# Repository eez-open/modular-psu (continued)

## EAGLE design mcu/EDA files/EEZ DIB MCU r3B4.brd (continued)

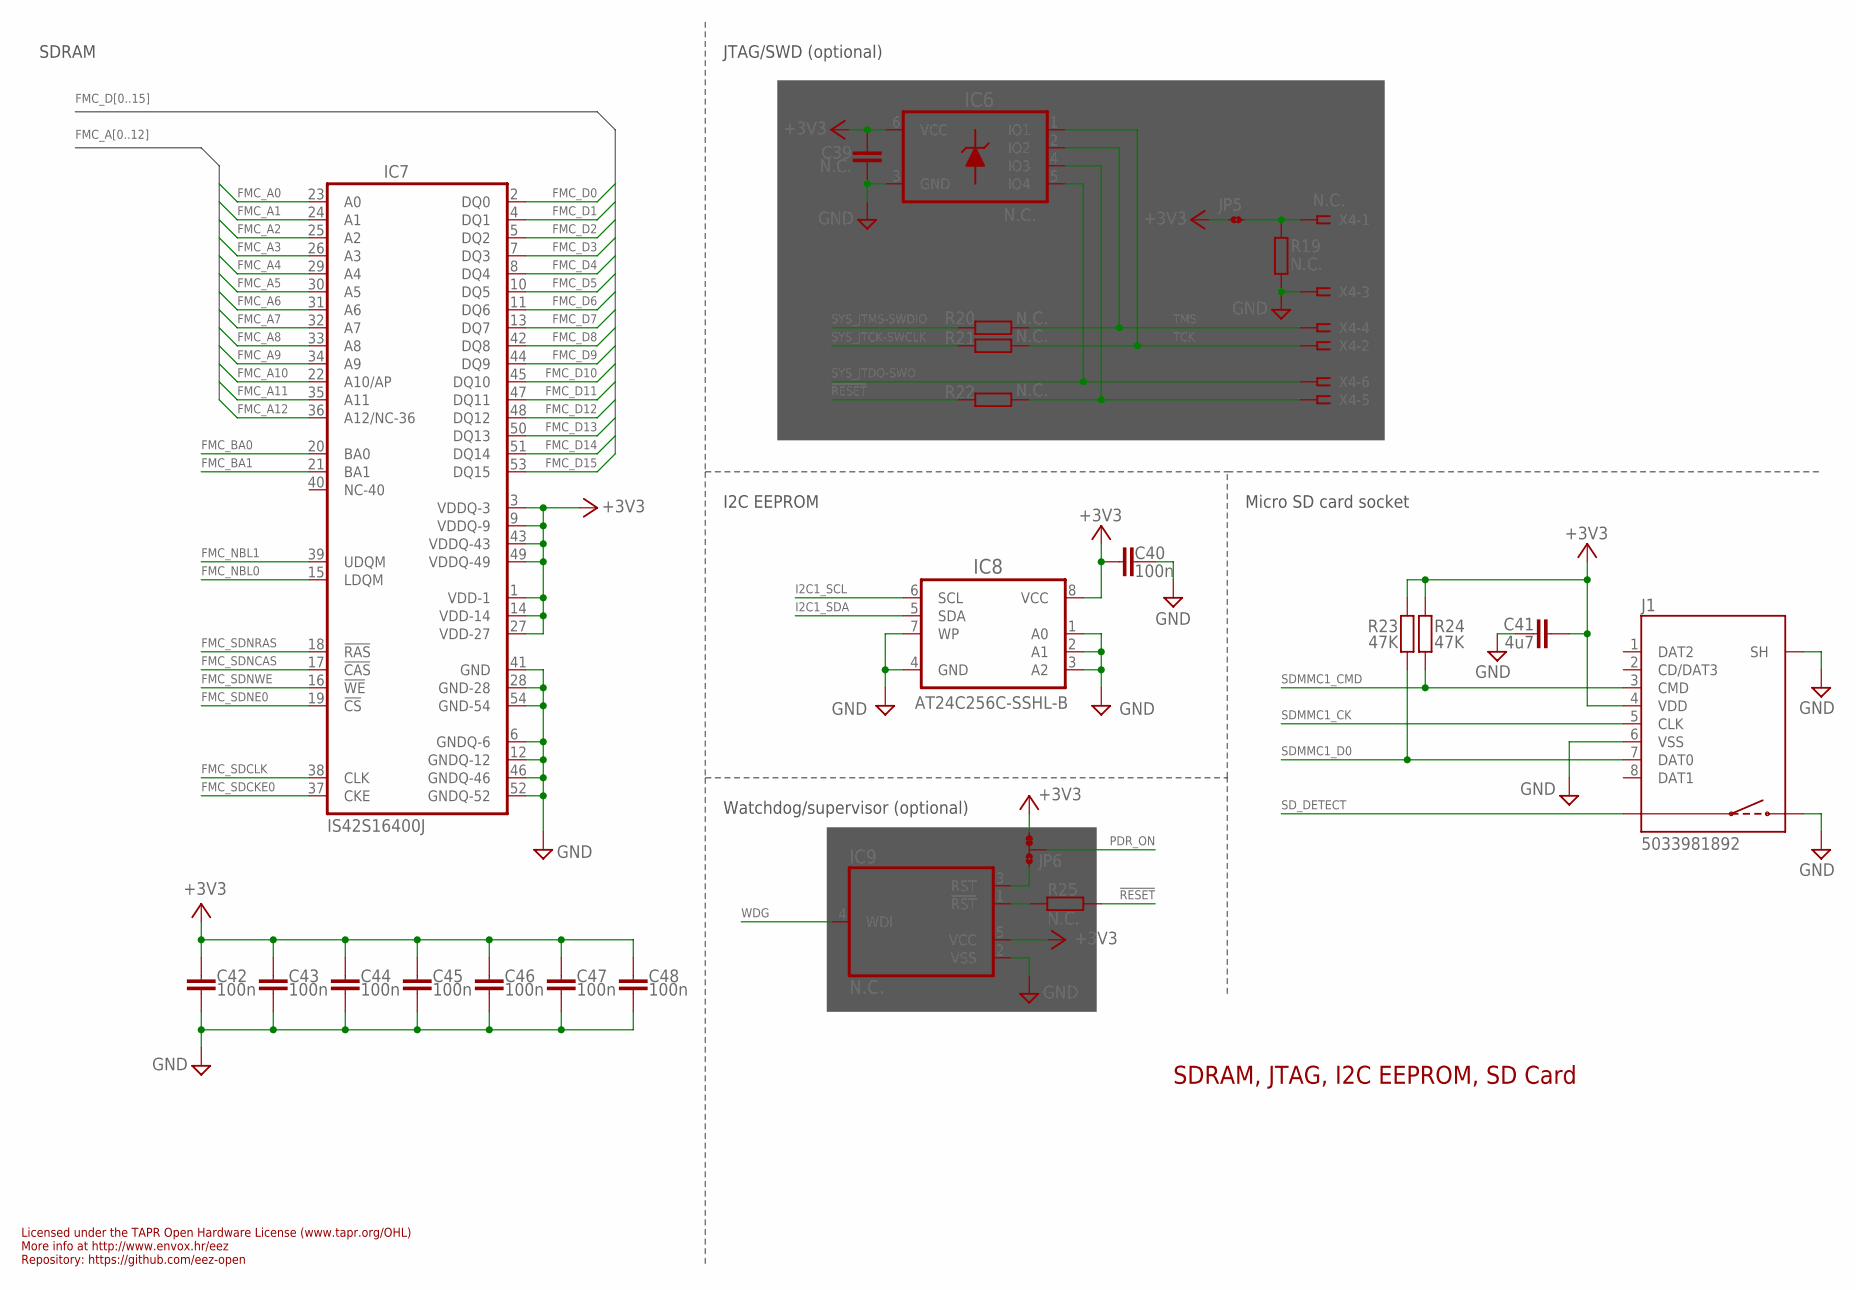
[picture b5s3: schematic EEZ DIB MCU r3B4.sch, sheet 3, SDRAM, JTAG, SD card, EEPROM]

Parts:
C39: N.C.; C0603
C40, C42, C43, C44, C45, C46, C47, C48: 100n; C0603
C41: 4u7; C1206
IC6: N.C.; DRL6
IC7: IS42S16400J; TSOPII-54
IC8: AT24C256C-SSHL-B; SOIC127P600X173-8N
IC9: N.C.; SOT23-5L_STM
J1: 5033981892; 5033981892-PCBA
JP5: JP2-CUT
JP6: JP3-CUT-0805-ROTATED; JP3-0805-CUT2
R19, R20, R21, R22, R25: N.C.; R0805
R23, R24: 47K; R0805
X4: N.C.; SSW-106-02-S-S

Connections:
!RESET: R22.1, R25.2; also elsewhere on the board
+3V3: C39.1, C40.2, C41.1, C42.1, C43.1, C44.1, C45.1, C46.1, C47.1, C48.1, IC6.6 (VCC), IC7.1 (VDD-1), IC7.3 (VDDQ-3), IC7.9 (VDDQ-9), IC7.14 (VDD-14), IC7.27 (VDD-27), IC7.43 (VDDQ-43), IC7.49 (VDDQ-49), IC8.8 (VCC), IC9.5 (VCC), J1.4 (VDD), JP5.1, JP6.NC, R23.1, R24.1; also elsewhere on the board
FMC_A0: IC7.23 (A0); also elsewhere on the board
FMC_A1: IC7.24 (A1); also elsewhere on the board
FMC_A2: IC7.25 (A2); also elsewhere on the board
FMC_A3: IC7.26 (A3); also elsewhere on the board
FMC_A4: IC7.29 (A4); also elsewhere on the board
FMC_A5: IC7.30 (A5); also elsewhere on the board
FMC_A6: IC7.31 (A6); also elsewhere on the board
FMC_A7: IC7.32 (A7); also elsewhere on the board
FMC_A8: IC7.33 (A8); also elsewhere on the board
FMC_A9: IC7.34 (A9); also elsewhere on the board
FMC_A10: IC7.22 (A10/AP); also elsewhere on the board
FMC_A11: IC7.35 (A11); also elsewhere on the board
FMC_A12: IC7.36 (A12/NC-36); also elsewhere on the board
FMC_BA0: IC7.20 (BA0); also elsewhere on the board
FMC_BA1: IC7.21 (BA1); also elsewhere on the board
FMC_D0: IC7.2 (DQ0); also elsewhere on the board
FMC_D1: IC7.4 (DQ1); also elsewhere on the board
FMC_D2: IC7.5 (DQ2); also elsewhere on the board
FMC_D3: IC7.7 (DQ3); also elsewhere on the board
FMC_D4: IC7.8 (DQ4); also elsewhere on the board
FMC_D5: IC7.10 (DQ5); also elsewhere on the board
FMC_D6: IC7.11 (DQ6); also elsewhere on the board
FMC_D7: IC7.13 (DQ7); also elsewhere on the board
FMC_D8: IC7.42 (DQ8); also elsewhere on the board
FMC_D9: IC7.44 (DQ9); also elsewhere on the board
FMC_D10: IC7.45 (DQ10); also elsewhere on the board
FMC_D11: IC7.47 (DQ11); also elsewhere on the board
FMC_D12: IC7.48 (DQ12); also elsewhere on the board
FMC_D13: IC7.50 (DQ13); also elsewhere on the board
FMC_D14: IC7.51 (DQ14); also elsewhere on the board
FMC_D15: IC7.53 (DQ15); also elsewhere on the board
FMC_NBL0: IC7.15 (LDQM); also elsewhere on the board
FMC_NBL1: IC7.39 (UDQM); also elsewhere on the board
FMC_SDCKE0: IC7.37 (CKE); also elsewhere on the board
FMC_SDCLK: IC7.38 (CLK); also elsewhere on the board
FMC_SDNCAS: IC7.17 (!CAS); also elsewhere on the board
FMC_SDNE0: IC7.19 (!CS); also elsewhere on the board
FMC_SDNRAS: IC7.18 (!RAS); also elsewhere on the board
FMC_SDNWE: IC7.16 (!WE); also elsewhere on the board
GND: C39.2, C40.1, C41.2, C42.2, C43.2, C44.2, C45.2, C46.2, C47.2, C48.2, IC6.3 (GND), IC7.6 (GNDQ-6), IC7.12 (GNDQ-12), IC7.28 (GND-28), IC7.41 (GND), IC7.46 (GNDQ-46), IC7.52 (GNDQ-52), IC7.54 (GND-54), IC8.1 (A0), IC8.2 (A1), IC8.3 (A2), IC8.4 (GND), IC8.7 (WP), IC9.2 (VSS), J1.6 (VSS), J1.S (SH), J1.S1 (SH), J1.S2 (SH), J1.S3 (SH), J1.SW2, R19.1, X4.3; also elsewhere on the board
I2C1_SCL: IC8.6 (SCL); also elsewhere on the board
I2C1_SDA: IC8.5 (SDA); also elsewhere on the board
unnamed: JP5.2, R19.2, X4.1
unnamed: IC9.3 (RST), JP6.NO
unnamed: IC9.1 (!RST), R25.1
PDR_ON: JP6.COM; also elsewhere on the board
SDMMC1_CK: J1.5 (CLK); also elsewhere on the board
SDMMC1_CMD: J1.3 (CMD), R24.2; also elsewhere on the board
SDMMC1_D0: J1.7 (DAT0), R23.2; also elsewhere on the board
SD_DETECT: J1.SW1; also elsewhere on the board
SWD_NRST: IC6.4 (IO3), R22.2, X4.5
SYS_JTCK-SWCLK: R21.1; also elsewhere on the board
SYS_JTDO-SWO: IC6.5 (IO4), X4.6; also elsewhere on the board
SYS_JTMS-SWDIO: R20.1; also elsewhere on the board
TCK: IC6.1 (IO1), R21.2, X4.2
TMS: IC6.2 (IO2), R20.2, X4.4
WDG: IC9.4 (WDI); also elsewhere on the board

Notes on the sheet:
SDRAM, JTAG, I2C EEPROM, SD Card
Licensed under the TAPR Open Hardware License (www.tapr.org/OHL)
Repository: https://github.com/eez-open
More info at http://www.envox.hr/eez
I2C EEPROM
Micro SD card socket
JTAG/SWD (optional)
SDRAM
Watchdog/supervisor (optional)

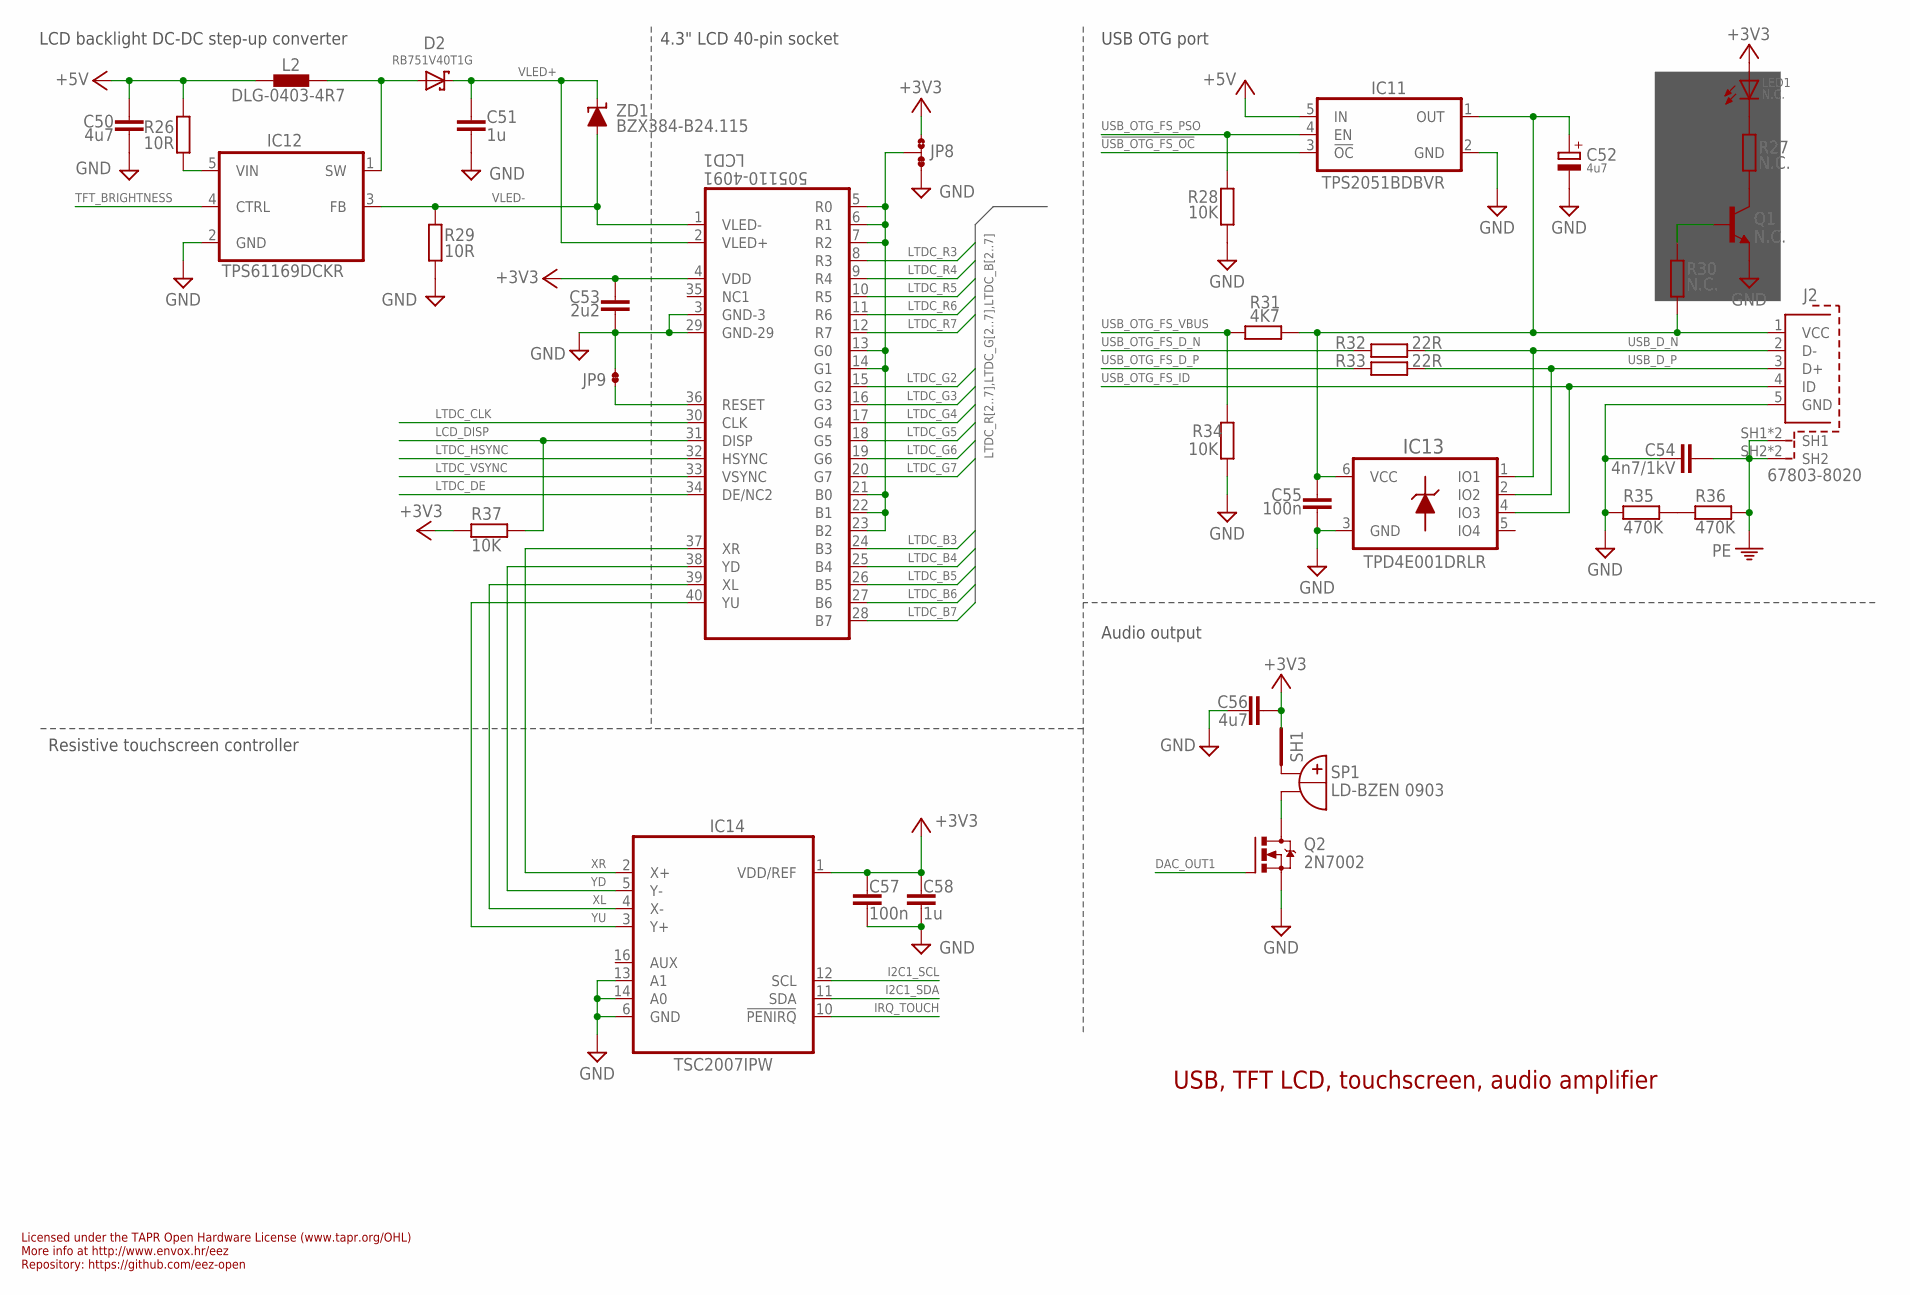
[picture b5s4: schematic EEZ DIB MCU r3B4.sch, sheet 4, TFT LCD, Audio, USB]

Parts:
C50, C56: 4u7; C1206
C51, C58: 1u; C0805
C52: 4u7; EC1206
C53: 2u2; C0805
C54: 4n7/1kV; C1812
C55, C57: 100n; C0603
D2: RB751V40T1G; SOD323-R
IC11: TPS2051BDBVR; DBV5
IC12: TPS61169DCKR; DCK5
IC13: TPD4E001DRLR; DRL6
IC14: TSC2007IPW; PW(R-PDSO-G16)
J2: 67803-8020; 678038020
JP8: JP3-CUT-0805-ROTATED; JP3-0805-CUT2
JP9: JP2-NOCUT-0805; JP2-0805-NOCUT
L2: DLG-0403-4R7; DE0403
LCD1: 505110-4091; FPC_40
LED1: N.C.; LED_0805
Q1: N.C.; SOT23-BEC
Q2: 2N7002; SOT103P240X110-3N
R26, R29: 10R; R0805
R27, R30: N.C.; R0805
R28, R34, R37: 10K; R0805
R31: 4K7; R0805
R32, R33: 22R; R0805
R35, R36: 470K; R0805
SH1: SHORTNOHOLE; SHORT_NOHOLE
SP1: LD-BZEN 0903; LD-BZEN_COMBO
ZD1: BZX384-B24.115; SOD323-W

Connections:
!USB_OTG_FS_OC: IC11.3 (!OC); also elsewhere on the board
+3V3: C53.1, C56.2, C57.2, C58.2, IC14.1 (VDD/REF), JP8.NO, LCD1.4 (VDD), LED1.A, R37.2, SH1.P$2 (GND_B); also elsewhere on the board
+5V: C50.1, IC11.5 (IN), L2.1, R26.1; also elsewhere on the board
DAC_OUT1: Q2.1 (G); also elsewhere on the board
GND: C50.2, C51.2, C52.-, C53.2, C54.1, C55.1, C56.1, C57.1, C58.1, IC11.2 (GND), IC12.2 (GND), IC13.3 (GND), IC14.6 (GND), IC14.13 (A1), IC14.14 (A0), J2.5 (GND), JP8.NC, JP9.2, LCD1.3 (GND-3), LCD1.29 (GND-29), Q1.E, Q2.2 (S), R28.1, R29.2, R34.2, R35.2; also elsewhere on the board
I2C1_SCL: IC14.12 (SCL); also elsewhere on the board
I2C1_SDA: IC14.11 (SDA); also elsewhere on the board
IRQ_TOUCH: IC14.10 (!PENIRQ); also elsewhere on the board
LCD_DISP: LCD1.31 (DISP), R37.1
LTDC_B3: LCD1.24 (B3); also elsewhere on the board
LTDC_B4: LCD1.25 (B4); also elsewhere on the board
LTDC_B5: LCD1.26 (B5); also elsewhere on the board
LTDC_B6: LCD1.27 (B6); also elsewhere on the board
LTDC_B7: LCD1.28 (B7); also elsewhere on the board
LTDC_CLK: LCD1.30 (CLK); also elsewhere on the board
LTDC_DE: LCD1.34 (DE/NC2); also elsewhere on the board
LTDC_G2: LCD1.15 (G2); also elsewhere on the board
LTDC_G3: LCD1.16 (G3); also elsewhere on the board
LTDC_G4: LCD1.17 (G4); also elsewhere on the board
LTDC_G5: LCD1.18 (G5); also elsewhere on the board
LTDC_G6: LCD1.19 (G6); also elsewhere on the board
LTDC_G7: LCD1.20 (G7); also elsewhere on the board
LTDC_HSYNC: LCD1.32 (HSYNC); also elsewhere on the board
LTDC_R3: LCD1.8 (R3); also elsewhere on the board
LTDC_R4: LCD1.9 (R4); also elsewhere on the board
LTDC_R5: LCD1.10 (R5); also elsewhere on the board
LTDC_R6: LCD1.11 (R6); also elsewhere on the board
LTDC_R7: LCD1.12 (R7); also elsewhere on the board
LTDC_VSYNC: LCD1.33 (VSYNC); also elsewhere on the board
unnamed: LED1.C, R27.2
unnamed: JP8.COM, LCD1.5 (R0), LCD1.6 (R1), LCD1.7 (R2), LCD1.13 (G0), LCD1.14 (G1), LCD1.21 (B0), LCD1.22 (B1), LCD1.23 (B2)
unnamed: Q2.3 (D), SP1.-, SP1.-B (-)
unnamed: Q1.C, R27.1
unnamed: Q1.B, R30.2
unnamed: SH1.P$1 (GND_A), SP1.+, SP1.+B (+)
unnamed: JP9.1, LCD1.36 (RESET)
unnamed: IC12.5 (VIN), R26.2
unnamed: R35.1, R36.2
PE: C54.2, J2.SH1, J2.SH1.1 (SH1), J2.SH2, J2.SH2.2 (SH2), R36.1; also elsewhere on the board
SW_WLED: D2.A, IC12.1 (SW), L2.2
TFT_BRIGHTNESS: IC12.4 (CTRL); also elsewhere on the board
USB_D_N: IC13.1 (IO1), J2.2 (D-), R32.1
USB_D_P: IC13.2 (IO2), J2.3 (D+), R33.1
USB_OTG_FS_D_N: R32.2; also elsewhere on the board
USB_OTG_FS_D_P: R33.2; also elsewhere on the board
USB_OTG_FS_ID: IC13.4 (IO3), J2.4 (ID); also elsewhere on the board
USB_OTG_FS_PSO: IC11.4 (EN), R28.2; also elsewhere on the board
USB_OTG_FS_VBUS: R31.2, R34.1; also elsewhere on the board
USB_VBUS: C52.+, C55.2, IC11.1 (OUT), IC13.6 (VCC), J2.1 (VCC), R30.1, R31.1
VLED+: C51.1, D2.C, LCD1.2 (VLED+), ZD1.C
VLED-: IC12.3 (FB), LCD1.1 (VLED-), R29.1, ZD1.A
XL: IC14.4 (X-), LCD1.39 (XL)
XR: IC14.2 (X+), LCD1.37 (XR)
YD: IC14.5 (Y-), LCD1.38 (YD)
YU: IC14.3 (Y+), LCD1.40 (YU)

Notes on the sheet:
USB, TFT LCD, touchscreen, audio amplifier
Licensed under the TAPR Open Hardware License (www.tapr.org/OHL)
Repository: https://github.com/eez-open
More info at http://www.envox.hr/eez
4.3" LCD 40-pin socket
LCD backlight DC-DC step-up converter
USB OTG port
Resistive touchscreen controller
Audio output

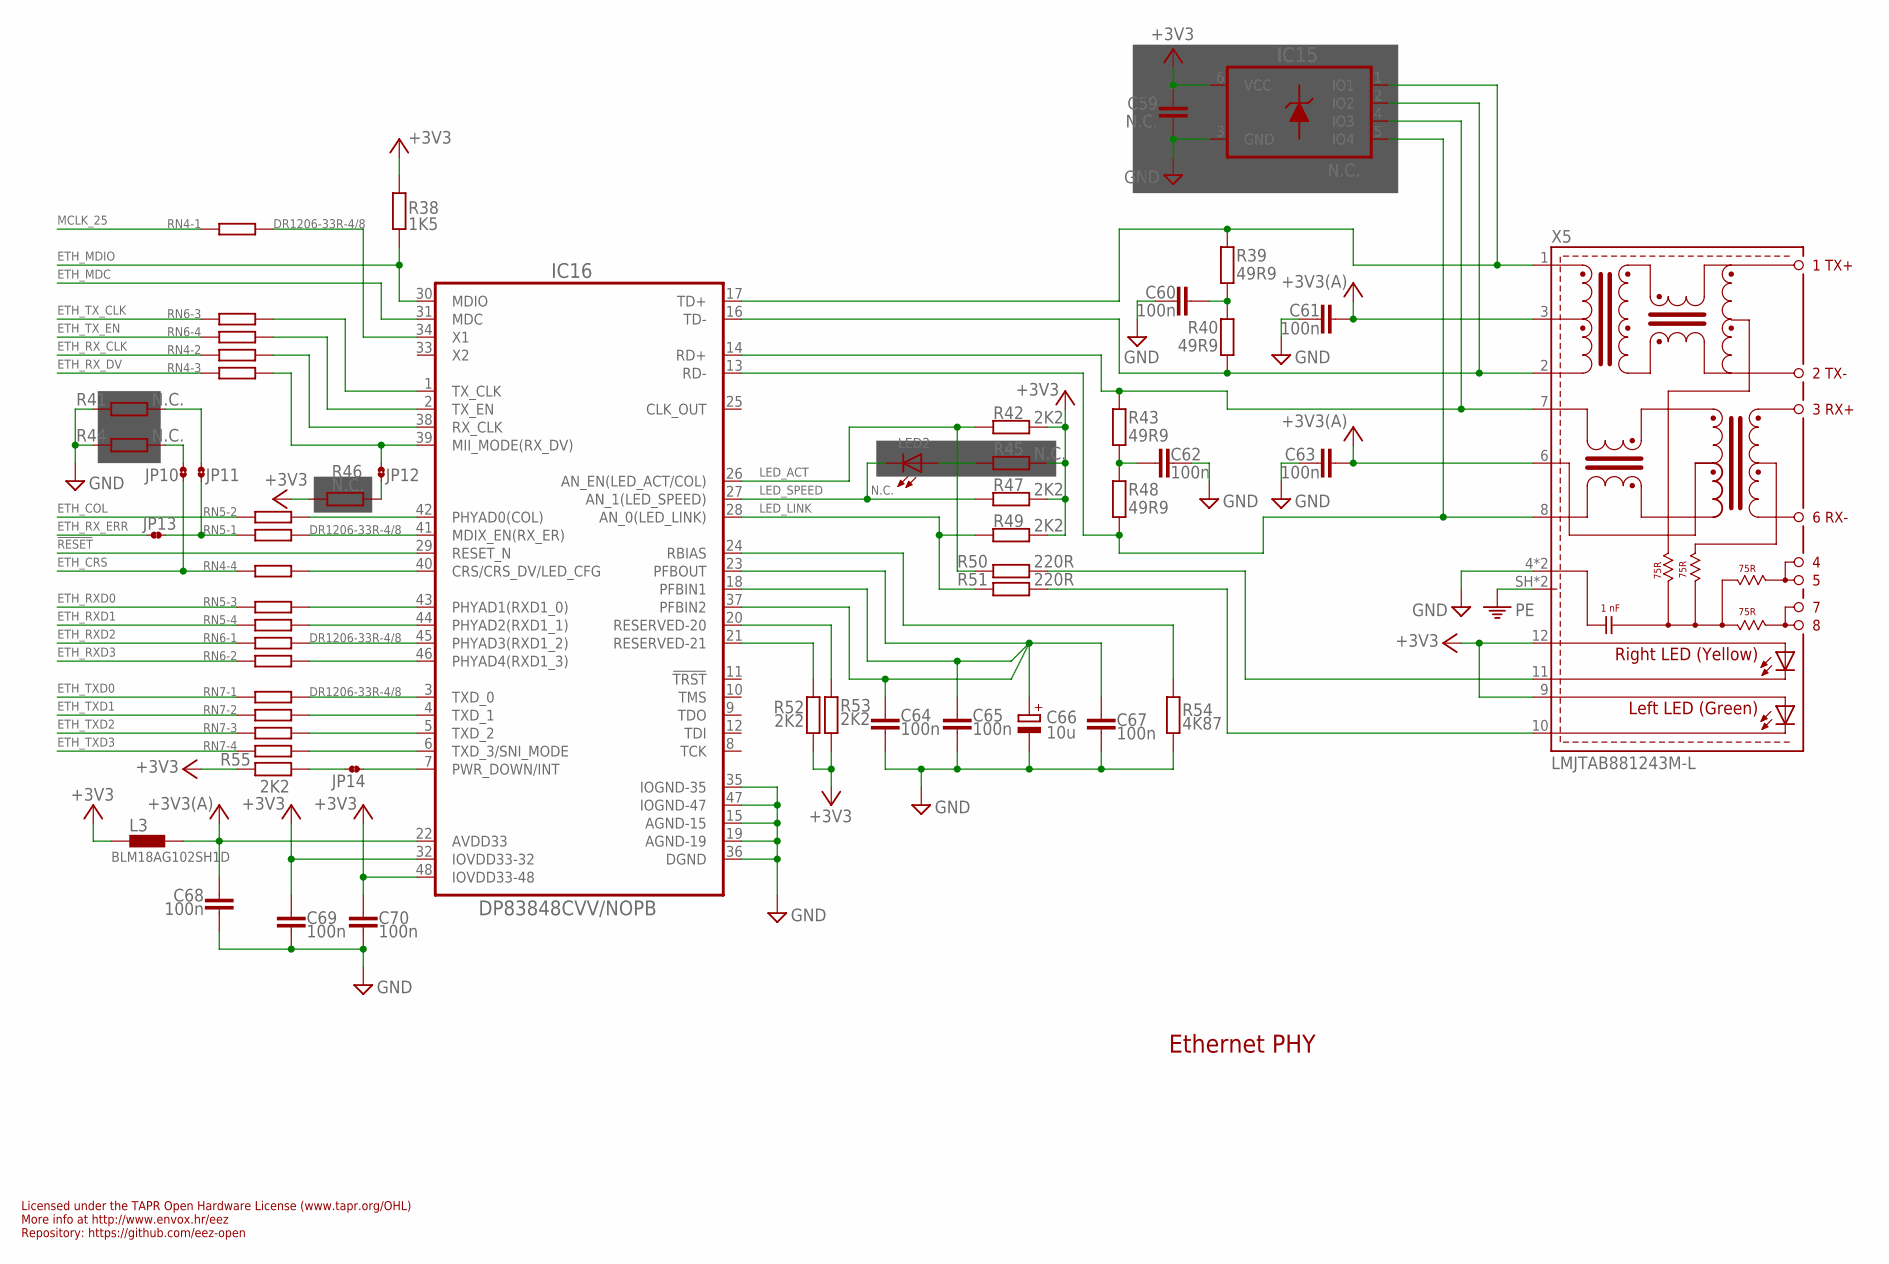
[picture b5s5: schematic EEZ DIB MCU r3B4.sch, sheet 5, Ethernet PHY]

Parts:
C59: N.C.; C0603
C60, C61, C62, C63, C64, C65, C67, C68, C69, C70: 100n; C0603
C66: 10u; EC1206
IC15: N.C.; DRL6
IC16: DP83848CVV/NOPB; PT48
JP10, JP11, JP12: JP2-CUT
JP13, JP14: JP2-NOCUT
L3: BLM18AG102SH1D; BEAD0603
LED2: N.C.; LED_0805
R38: 1K5; R0805
R39, R40, R43, R48: 49R9; R0805
R41, R44, R45, R46: N.C.; R0805
R42, R47, R49, R52, R53, R55: 2K2; R0805
R50, R51: 220R; R0805
R54: 4K87; R0805
RN4, RN5, RN6, RN7: DR1206-33R-4/8; CAY16
X5: LMJTAB881243M-L; RJ45-TRAFO-LED

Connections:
!RESET: IC16.29 (RESET_N); also elsewhere on the board
+3V3: C59.1, C69.1, C70.1, IC15.6 (VCC), IC16.32 (IOVDD33-32), IC16.48 (IOVDD33-48), L3.P$1 (1), R38.2, R42.1, R45.1, R46.1, R47.1, R49.1, R52.1, R53.1, R55.1, X5.9 (GREEN-A), X5.12 (YELLOW_A); also elsewhere on the board
+3V3(A): C61.2, C63.2, C68.1, IC16.22 (AVDD33), L3.P$2 (2), X5.3 (CT), X5.6 (CR)
ETH_COL: RN5.2 (1); also elsewhere on the board
ETH_CRS: JP10.1, RN4.4 (1); also elsewhere on the board
ETH_MDC: IC16.31 (MDC); also elsewhere on the board
ETH_MDIO: IC16.30 (MDIO), R38.1; also elsewhere on the board
ETH_RXD0: RN5.3 (1); also elsewhere on the board
ETH_RXD1: RN5.4 (1); also elsewhere on the board
ETH_RXD2: RN6.1; also elsewhere on the board
ETH_RXD3: RN6.2 (1); also elsewhere on the board
ETH_RX_CLK: RN4.2 (1); also elsewhere on the board
ETH_RX_DV: RN4.3 (1); also elsewhere on the board
ETH_RX_ER: JP11.1, JP13.1, RN5.1
ETH_RX_ERR: JP13.2; also elsewhere on the board
ETH_TXD0: RN7.1; also elsewhere on the board
ETH_TXD1: RN7.2 (1); also elsewhere on the board
ETH_TXD2: RN7.3 (1); also elsewhere on the board
ETH_TXD3: RN7.4 (1); also elsewhere on the board
ETH_TX_CLK: RN6.3 (1); also elsewhere on the board
ETH_TX_EN: RN6.4 (1); also elsewhere on the board
GND: C59.2, C60.2, C61.1, C62.2, C63.1, C64.2, C65.2, C66.-, C67.2, C68.2, C69.2, C70.2, IC15.3 (GND), IC16.15 (AGND-15), IC16.19 (AGND-19), IC16.35 (IOGND-35), IC16.36 (DGND), IC16.47 (IOGND-47), R41.1, R44.1, R54.1, X5.4 (GND), X5.5 (GND); also elsewhere on the board
LED_ACT: IC16.26 (AN_EN(LED_ACT/COL)), R42.2, R50.2
LED_LINK: IC16.28 (AN_0(LED_LINK)), R49.2, R51.2
LED_SPEED: IC16.27 (AN_1(LED_SPEED)), LED2.C, R47.2
MCLK_25: RN4.1; also elsewhere on the board
unnamed: IC16.1 (TX_CLK), RN6.6 (2)
unnamed: C60.1, R39.1, R40.2
unnamed: R50.1, X5.11 (YELLOW-C)
unnamed: R51.1, X5.10 (GREEN-C)
unnamed: IC16.2 (TX_EN), RN6.5 (2)
unnamed: IC16.39 (MII_MODE(RX_DV)), JP12.2, RN4.6 (2)
unnamed: IC16.38 (RX_CLK), RN4.7 (2)
unnamed: IC16.3 (TXD_0), RN7.8 (2)
unnamed: IC16.4 (TXD_1), RN7.7 (2)
unnamed: IC16.5 (TXD_2), RN7.6 (2)
unnamed: IC16.34 (X1), RN4.8 (2)
unnamed: JP12.1, R46.2
unnamed: JP10.2, R44.2
unnamed: JP11.2, R41.2
unnamed: IC16.7 (PWR_DOWN/INT), JP14.2
unnamed: JP14.1, R55.2
unnamed: IC16.6 (TXD_3/SNI_MODE), RN7.5 (2)
unnamed: IC16.46 (PHYAD4(RXD1_3)), RN6.7 (2)
unnamed: IC16.45 (PHYAD3(RXD1_2)), RN6.8 (2)
unnamed: IC16.42 (PHYAD0(COL)), RN5.7 (2)
unnamed: IC16.44 (PHYAD2(RXD1_1)), RN5.5 (2)
unnamed: IC16.43 (PHYAD1(RXD1_0)), RN5.6 (2)
unnamed: IC16.41 (MDIX_EN(RX_ER)), RN5.8 (2)
unnamed: IC16.40 (CRS/CRS_DV/LED_CFG), RN4.5 (2)
unnamed: IC16.24 (RBIAS), R54.2
unnamed: IC16.21 (RESERVED-21), R52.2
unnamed: IC16.20 (RESERVED-20), R53.2
unnamed: LED2.A, R45.2
unnamed: C62.1, R43.1, R48.2
PE: X5.SH, X5.SH2 (SH); also elsewhere on the board
PFBOUT: C64.1, C65.1, C66.+, C67.1, IC16.18 (PFBIN1), IC16.23 (PFBOUT), IC16.37 (PFBIN2)
RD+: IC15.4 (IO3), IC16.14 (RD+), R43.2, X5.7 (RD+)
RD-: IC15.5 (IO4), IC16.13 (RD-), R48.1, X5.8 (RD-)
TD+: IC15.1 (IO1), IC16.17 (TD+), R39.2, X5.1 (TD+)
TD-: IC15.2 (IO2), IC16.16 (TD-), R40.1, X5.2 (TD-)

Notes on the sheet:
Ethernet PHY
Licensed under the TAPR Open Hardware License (www.tapr.org/OHL)
Repository: https://github.com/eez-open
More info at http://www.envox.hr/eez

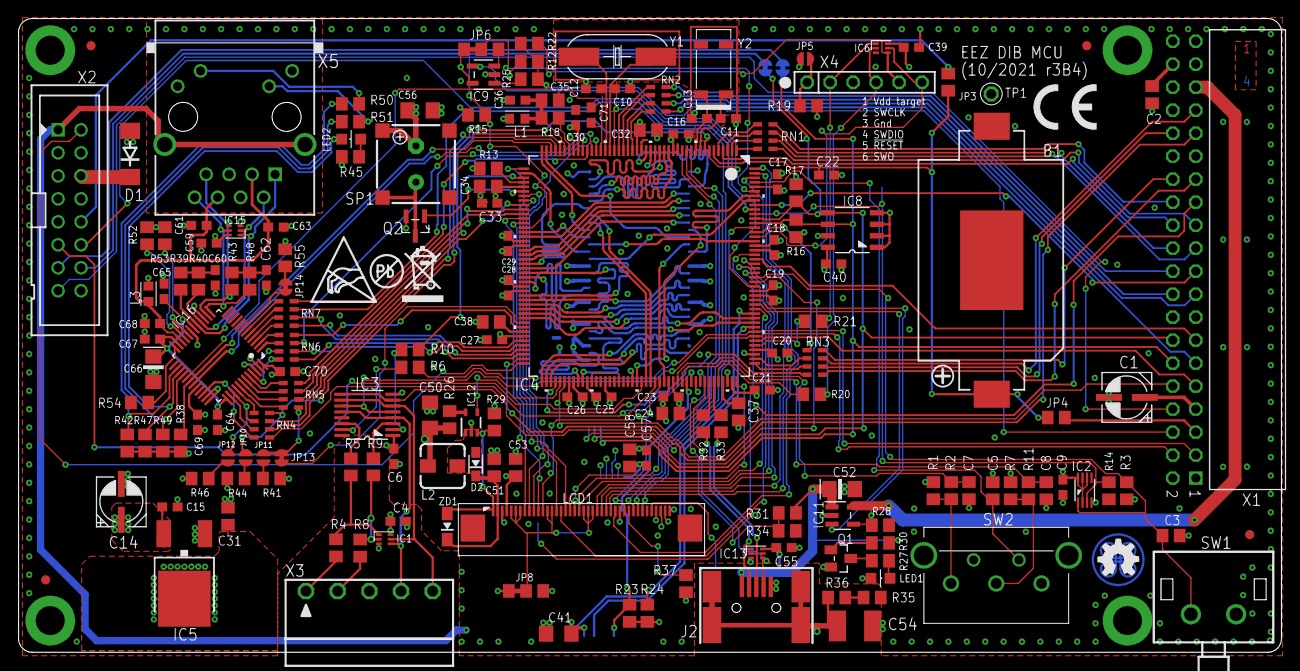
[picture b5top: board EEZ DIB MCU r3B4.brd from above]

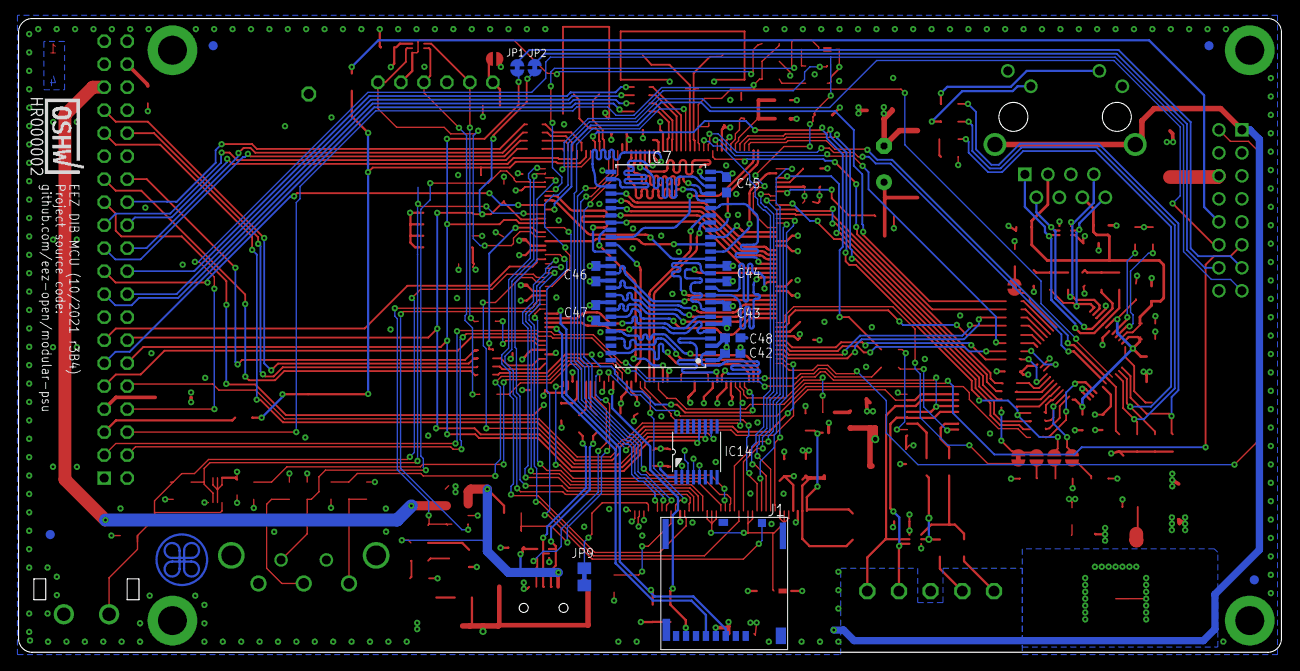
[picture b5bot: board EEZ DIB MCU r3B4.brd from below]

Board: 4 copper layers, 139.5 x 70.0 mm, 200 parts (19 on the bottom side), 239 nets.

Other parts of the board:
EEZ_SIGNATURE: SIGNATURESMALL; SIGNATURE_5MM
U$1: RECYCLE_BIN1/8
U$3: CE_5MM
U$5: PB_SMALL
U$6: ESD_SYMBOL

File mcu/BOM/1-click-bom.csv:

References,Qty,Description,Manufacturer,MPN,Manufacturer,MPN,Manufacturer,MPN,Manufacturer,MPN,Digikey,Mouser,RS,Newark,Farnell
B1,1,DS1092-10-W6L,,732-12325-1-ND,,79527141,,DS1092-10-W6L,,,,,,,
"C1, C14",2,EEEFK1V220R,,EEEFK1V220R,,,,,,,,,,,
"C10, C12",2,18p,,VJ0603A180JXACW1BC,,1276-1089-1-ND,,C0603C180J5GACTU,,CL10C180JB8NNNC,,,,,
"C11, C13",2,4p7,,MC0603N4R7C500CT,,311-1740-1-ND,,C0603C479C5GACTU,,CL10C4R7CB8NNNC,,,,,
"C2, C31, C32, C37, C38, C53",6,2u2,,GRM21BR71C225KA12L,,1276-2954-1-ND,,CL21B225KAFNNNF,,CL21B225KOFNNNG,,,,,
"C24, C34, C35, C51, C58",5,1u,,885012207078,,1276-1066-1-ND,,08052R104K8BB,,VJ0805Y105KXXTW1BC,,,,,
"C3, C5, C7, C8",4,10n,,VJ0805Y103JXXPW1BC,,490-7194-1-ND,,08055C103KAT2A,,CC0805KRX7R9103,,,,,
"C4, C6, C9, C15, C16, C17, C18, C19, C20, C21, C22, C23, C25, C26, C27, C28, C29, C30, C33, C36, C40, C42, C43, C44, C45, C46, C47, C48, C55, C57, C60, C61, C62, C63, C64, C65, C67, C68, C69, C70",40,100n,,C0603C104K4RAC7081,,490-4774-1-ND,,C0603C104K4RACTU,,CL10B104KA8NNNC,,,,,
"C41, C50, C56",3,4u7,,C3216X7R1E475K160AC,,1276-2970-1-ND,,C1206C475K3RACTU,,GCM31CR71E475KA55L,,,,,
C52,1,4u7/6.3V,,T491A475K006AT,,399-9717-1-ND,,T491A475K006AT,,T491A475K006AT,,,,,
C54,1,4n7/1kV,,885342211001,,732-12143-1-ND,,1812GC472KAT2A,,1812B472K202CT,,,,,
C66,1,10u,,T491A106K006AT,,399-3683-1-ND,,F930J106MA,,T491A106K006AT,,,,,
D1,1,SMBJ5.0A-TR,,SMBJ5.0ATR,,497-3144-1-ND,,SMBJ5.0A-TR,,SMBJ5.0A-TR,,,,,
D2,1,RB751V40T1G,,RB751V40T1G,,RB751V40T1GOSCT-ND,,RB751V40T1G,,RB751V40T1G,,,,,
"IC1, IC13",2,TPD4E001DRLR,,TPD4E001DRLR,,296-21887-1-ND,,TPD4E001DRLR,,-,,,,,
IC11,1,TPS2051BDBVR,,TPS2051BDBVR,,296-21265-1-ND,,TPS2051BDBVT,,-,,,,,
IC12,1,TPS61169DCKR,,TPS61169DCKR,,296-40821-1-ND,,-,,,,,,,
IC14,1,TSC2007IPW,,TSC2007IPWR,,296-27124-1-ND,,TSC2007IPW,,-,,,,,
IC16,1,DP83848CVV/NOPB,,DP83848CVV/NOPB,,DP83848CVV/NOPB-ND,,DP83848CVV/NOPB,,DP83848CVV/NOPB,,,,,
IC2,1,74AUP1G74DC.125,,"74AUP1G74DC,125",,1727-6029-1-ND,,"74AUP1G74DC,125",,74AUP1G74DC.125,,,,,
IC3,1,CD74HC4050PWR,,CD74HC4050PW,,296-9215-1-ND,,CD74HC4050PWR,,-,,,,,
IC4,1,STM32F769IIT6,,STM32F769IIT6,,497-16649-ND,,STM32F769IIT6,,,,,,,
IC5,1,LD1117ADT33TR,,LD1117ADT33TR,,497-3455-1-ND,,LD1117ADT33TR,,LD1117ADT33,,,,,
IC7,1,IS42S16400J,,IS42S16400J-6TLI,,IS42S16400J-7TLI,,IS42S16400J-7TLI,,IS42S16400J-7TL,,,,,
IC8,1,AT24C256C-SSHL-B,,AT24C256C-SSHL-B,,AT24C256C-SSHL-B-ND,,AT24C256C-SSHL-B,,AT24C256C-SSHL-B,,,,,
J1,1,503398-1892,,503398-1892,,WM11190CT-ND,,503398-1892,,MX-503398-1892,,,,,
J2,1,67803-8020,,67803-8020,,WM17148CT-ND,,67803-8020,,MX-67803-8020,,,,,
"L1, L3",2,BLM18AG102SH1D,,MMZ1608Y102B,,490-7809-1-ND,,BLM18AG102SH1D,,BLM18AG102SH1D,,,,,
L2,1,DLG-0403-4R7,,SDR0403-4R7ML,,SDR0403-4R7MLCT-ND,,DLG-0403-4R7,,,,,,,
LCD1,1,505110-4091,,505110-4091,,WM11292CT-ND,,-,,,,,,,
Q2,1,2N27002,,2N7002-7-F,,2N7002LT1GOSCT-ND,,2N7002LT1G,,2N7002LT1G,,,,,
"R1, R4, R5, R7, R8, R9, R15, R31",8,4K7,,CRGCQ0805F4K7,,311-4.70KCRCT-ND,,CRG0805F4K7,,SMD0805-4K7-1%,,,,,
"R16, R17, R38",3,1K5,,CRGCQ0805J1K5,,541-4161-1-ND,,CRG0805F1K5,,SMD0805-1K5-1%,,,,,
R18,1,47R,,CRGCQ0805J47R,,P47.0CCT-ND,,CRG0805F47R,,SMD0805-47R-1%,,,,,
"R2, R3, R11, R13, R28, R34, R37",7,10K,,RC0805FR-0710KL,,311-10.0KCRCT-ND,,CRG0805F10K,,RC0805FR-0710K,,,,,
"R22, R23",2,47K,,MCWR08X4702FTL,,RHM47KKCT-ND,,CRCW080547K0FKEA,,SMD0805-47K-1%,,,,,
"R26, R29",2,10R,,MCWR08X10R0FTL,,311-10.0CRCT-ND,,CRG0805F10R,,0805S8F100JT5E,,,,,
"R32, R33",2,22R,,MCWR08X22R0FTL,,311-22.0CRCT-ND,,CRG0805F22R,,0805S8F220JT5E,,,,,
"R35, R36",2,470K,,MCWR08X4703FTL,,A126370CT-ND,,CRG0805F470K,,0805S8J0474T5E,,,,,
"R39, R40, R43, R48",4,49R9,,MCWR08X49R9FTL,,311-49.9CRCT-ND,,CRCW080549R9FKEA,,RC0805FR-0749R9,,,,,
"R42, R47, R49, R52, R53, R55",6,2K2,,RC0805FR-072K2L,,311-2.20KCRCT-ND,,CRCW08052K20FKEA,,SMD0805-2K2-1%,,,,,
"R50, R51",2,220R,,WCR0805-220RFI,,RMCF0805FT220RCT-ND,,CRG0805F220R,,0805S8F2200T5E,,,,,
R54,1,4K87,,CRCW08054K87FKEA,,311-4.87KCRCT-ND,,RC0805FR-074K87,,,,,,,
"R6, R10",2,1K,,WCR0805-1K0FI,,RC0805FR-071KL,,CRG0805F1K0,,SMD0805-1K-1%,,,,,
"RN1, RN2, RN3, RN4, RN5, RN6, RN7",7,DR1206-33R-4/8,,CAY16-330J4LF,,CAY16-330J4LFCT-ND,,CAY16-330J4LF,,DR1206-33R-4/8,,,,,
SP1,1,LD-BZEN 0903,,-,,LD-BZEN-0903,,,,,,,,,
SW1,1,TL1100CF160Q,,TL1100CF160Q,,EG1822-ND,,-,,,,,,,
SW2,1,PEC16-2215F-S0024,,PEC16-2215F-S0024-ND,,-,,,,,,,,,
X1,1,DS1024-2*20R0,,SSW-120-02-T-D-RA,,SAM11958-ND,,SSW-120-02-F-D-RA,,DS1024-2*20R0,,,,,
X2,1,DS1013-16SSIB1,,MC-254-16-00-ST-DIP,,ED10523-ND,,61201621621,,DS1013-16SSIB1,,,,,
X3,1,691322110005,,CTB932HD/5,,732-2772-ND,,691322110005,,-,,,,,
X5,1,LMJTAB881243M-L or LMJ30288115CNL,,-,,LMJTAB881243M-L,,,,,,,,,
Y1,1,25 MHz,,LFXTAL033342,,1923-1536-1-ND,,LFXTAL010595,,25.00M-SMDHC49R,,,,,
Y2,1,XTAL016178-85SMX,,XTAL016178-85SMX,,1923-1021-1-ND,,LFXTAL016178,,32.768K-85SMXR,,,,,
ZD1,1,BZX384-B24.115,,MM3Z24VST1G,,1727-3645-1-ND,,BZT52C24S-7-F,,BZX384-B24.115,,,,,

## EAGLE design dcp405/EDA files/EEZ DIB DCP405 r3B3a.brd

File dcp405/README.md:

### Overview

_IMPORTANT: A crowdfunded version of the DCP405 module (r2B11) can be found [here](https://github.com/eez-open/modular-psu/tree/master/previous%20designs/dcp405%20r2B11%20(Crowd%20Supply%20edition))._

The EEZ DIB DCP405 Power module is modified EEZ H24005 [Power board](https://github.com/eez-open/psu-hw/tree/master/Power%20board) that can be housed in EEZ DIB chasis (e.g. _Bench Box 3_). It comes with PNP "pass" element, OVP with triac crowbar, SPI temperature sensor and redesigned down-programmer new power pre-regulator and bias power supply.

### Feature list
- Power input: 48 Vdc (e.g. Mean Well LRS-150F-48 or EPP-150-48)
- Max. output power: 155 W (as limited with Mean Well AC/DC module capacity) 
- Voltage regulation (CV), 0 – 40 V. Voltage set resolution (_U_SET_): 16-bit, read resolution (_U_MON_): 15-bit
- Current regulation (CC) with 2-range (50 mA, 5 A). Current set resolution (_I_SET_): 16-bit, Current read resolution (_I_MON_): 15-bit for each range
- On-board low EMI switching power pre-regulator and bias power supply
- On-board OVP with full range dual crowbar (triac/MOSFET) and two fuses
- Down-programmer
- Output enable (OE) circuit with LED indicator combined with coupling indication
- On-board Ø4 mm safety sockets (19 mm/0.75” pitch) 
- Pass-thru connector for power output coupling with other power boards for e.g. doubling output voltage (up to 80 V) or current (up to 10 A)
- Remote voltage sense with LED indicator and inverse polarity protection
- Remote voltage programming with LED indicator (+2.5 V for full range)
- Galvanically isolated SPI bus for communication with [MCU board](https://github.com/eez-open/modular-psu/tree/master/mcu)
- I2C EEPROM for storing board specific configuration and calibration parameters
- SPI Temperature sensor
- Dimensions: 180 x 95 mm, 4-layer PCB
- **CE certified design**

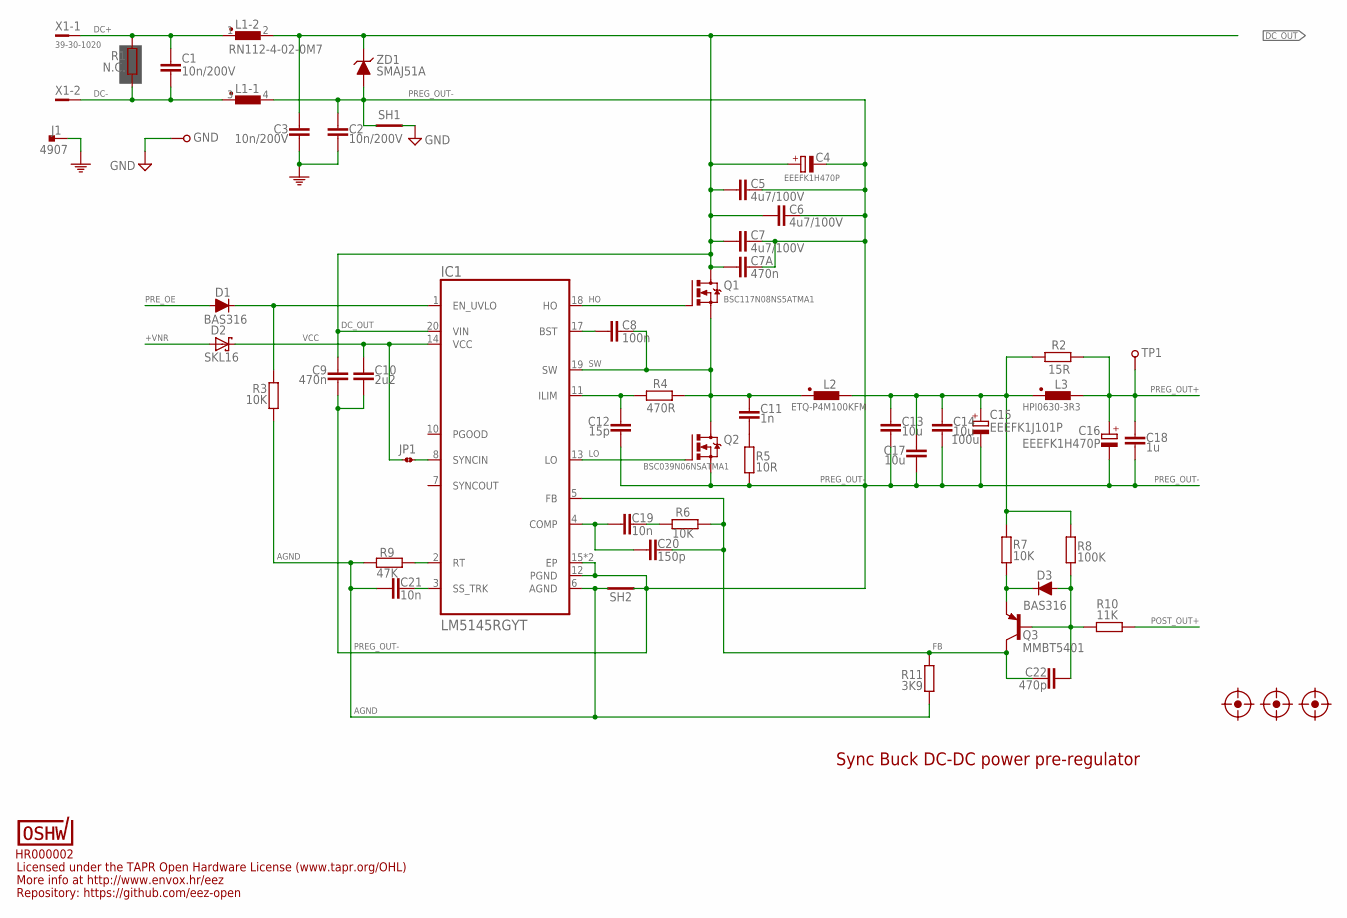
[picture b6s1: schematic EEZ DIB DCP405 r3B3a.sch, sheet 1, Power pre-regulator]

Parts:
C1, C2, C3: 10n/200V; C1206
C4, C16: EEEFK1H470P; CAPAE830X1050N
C5, C6, C7: 4u7/100V; C1210
C7A, C9: 470n; C0805
C8: 100n; C0603
C10: 2u2; C1206
C11: 1n; C0805
C12: 15p; C0805
C13, C14, C17: 10u; C1210
C15: EEEFK1J101P; CAPAE1030X1050N
C18: 1u; C0805
C19, C21: 10n; C0805
C20: 150p; C0805
C22: 470p; C0805
D1, D3: BAS316; SOD323-R
D2: SKL16; SOD123
FM1, FM2, FM3: FIDUCIAL_2; FIDUCIAL_DUAL
GND: PCB_TEST_TABSHIELD; PCB_SHIELD_TAB
IC1: LM5145RGYT; RGY0020B
J1: 4907; PCB_TAB-4907
JP1: JP2-CUT-0805; R_0805
L1: RN112-4-02-0M7; RN112
L2: ETQ-P4M100KFM; PANASONIC_ETQ-P4_KFM
L3: HPI0630-3R3; COILCRAFT_HPI0630
OSHWA: HR000002; CERT-SMALL-SILK
Q1: BSC117N08NS5ATMA1; TDSON-8
Q2: BSC039N06NSATMA1; TDSON-8
Q3: MMBT5401; SOT23-BEC
R1: N.C.; R2512
R2: 15R; R2010
R3, R6, R7: 10K; R0805
R4: 470R; R0805
R5: 10R; R1206
R8: 100K; R0805
R9: 47K; R0805
R10: 11K; R0805
R11: 3K9; R0805
SH1, SH2: SHORTNOHOLE; SHORT_NOHOLE
TP1: TEST-PIN_0.9MM
X1: 39-30-1020; MINIFIT_39301020
ZD1: SMAJ51A; DO214AA

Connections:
+VNR: D2.A; also elsewhere on the board
AGND: C21.2, IC1.6 (AGND), R3.1, R9.1, R11.2, SH2.1 (GND_A)
DC+: C1.2, L1.1, R1.2, X1.1
DC-: C1.1, L1.3 (1), R1.1, X1.2
DC_OUT: C3.2, C4.+, C5.1, C6.1, C7.1, C7A.2, C9.2, IC1.20 (VIN), L1.2, Q1.5 (D), Q1.6 (D), Q1.7 (D), Q1.8 (D), ZD1.C; also elsewhere on the board
FB: C20.1, C22.1, IC1.5 (FB), Q3.C, R6.2, R11.1
GND: GND.1, SH1.2 (GND_B); also elsewhere on the board
HO: IC1.18 (HO), Q1.4 (G)
LO: IC1.13 (LO), Q2.4 (G)
L_OUT: C13.1, C14.1, C15.+, C17.1, L2.2, L3.1, R2.2, R7.1, R8.1
unnamed: IC1.8 (SYNCIN), JP1.2
unnamed: D1.C, IC1.1 (EN_UVLO), R3.2
unnamed: D3.C, Q3.E, R7.2
unnamed: C19.1, R6.1
unnamed: C8.1, IC1.17 (BST)
unnamed: IC1.2 (RT), R9.2
unnamed: C19.2, C20.2, IC1.4 (COMP)
unnamed: C12.1, IC1.11 (ILIM), R4.1
unnamed: C21.1, IC1.3 (SS_TRK)
unnamed: C11.2, R5.2
unnamed: C22.2, D3.A, Q3.B, R8.2, R10.1
PE: C2.2, C3.1, J1.1, J1.2; also elsewhere on the board
POST_OUT+: R10.2; also elsewhere on the board
PREG_OUT+: C16.+, C18.2, L3.2, R2.1, TP1.1; also elsewhere on the board
PREG_OUT-: C2.1, C4.-, C5.2, C6.2, C7.2, C7A.1, C9.1, C10.1, C12.2, C13.2, C14.2, C15.-, C16.-, C17.2, C18.1, IC1.12 (PGND), IC1.15 (EP), IC1.21 (EP), L1.4 (2), Q2.1 (S), Q2.2 (S), Q2.3 (S), R5.1, SH1.1 (GND_A), SH2.2 (GND_B), ZD1.A; also elsewhere on the board
PRE_OE: D1.A; also elsewhere on the board
SW: C8.2, C11.1, IC1.19 (SW), L2.1, Q1.1 (S), Q1.2 (S), Q1.3 (S), Q2.5 (D), Q2.6 (D), Q2.7 (D), Q2.8 (D), R4.2
VCC: C10.2, D2.C, IC1.14 (VCC), JP1.1

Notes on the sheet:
Licensed under the TAPR Open Hardware License (www.tapr.org/OHL)
Repository: https://github.com/eez-open
More info at http://www.envox.hr/eez
Sync Buck DC-DC power pre-regulator
100u
